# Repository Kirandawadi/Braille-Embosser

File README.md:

An autonomous device built with **AVR** and programmed in **C** that can convert any printed textbook into braille format using **Optical Character Recognition (OCR)** and custom-built hardware mechanism.

It won the 2nd runner up at **AT-HACKATHON 2018**.

**Demo Video:** [Link](https://1drv.ms/v/c/b3eb1096e4f4a3a8/Eaij9OSWEOsggLN66wAAAAABXvvN7yaE1aCTUCs381BpYw)

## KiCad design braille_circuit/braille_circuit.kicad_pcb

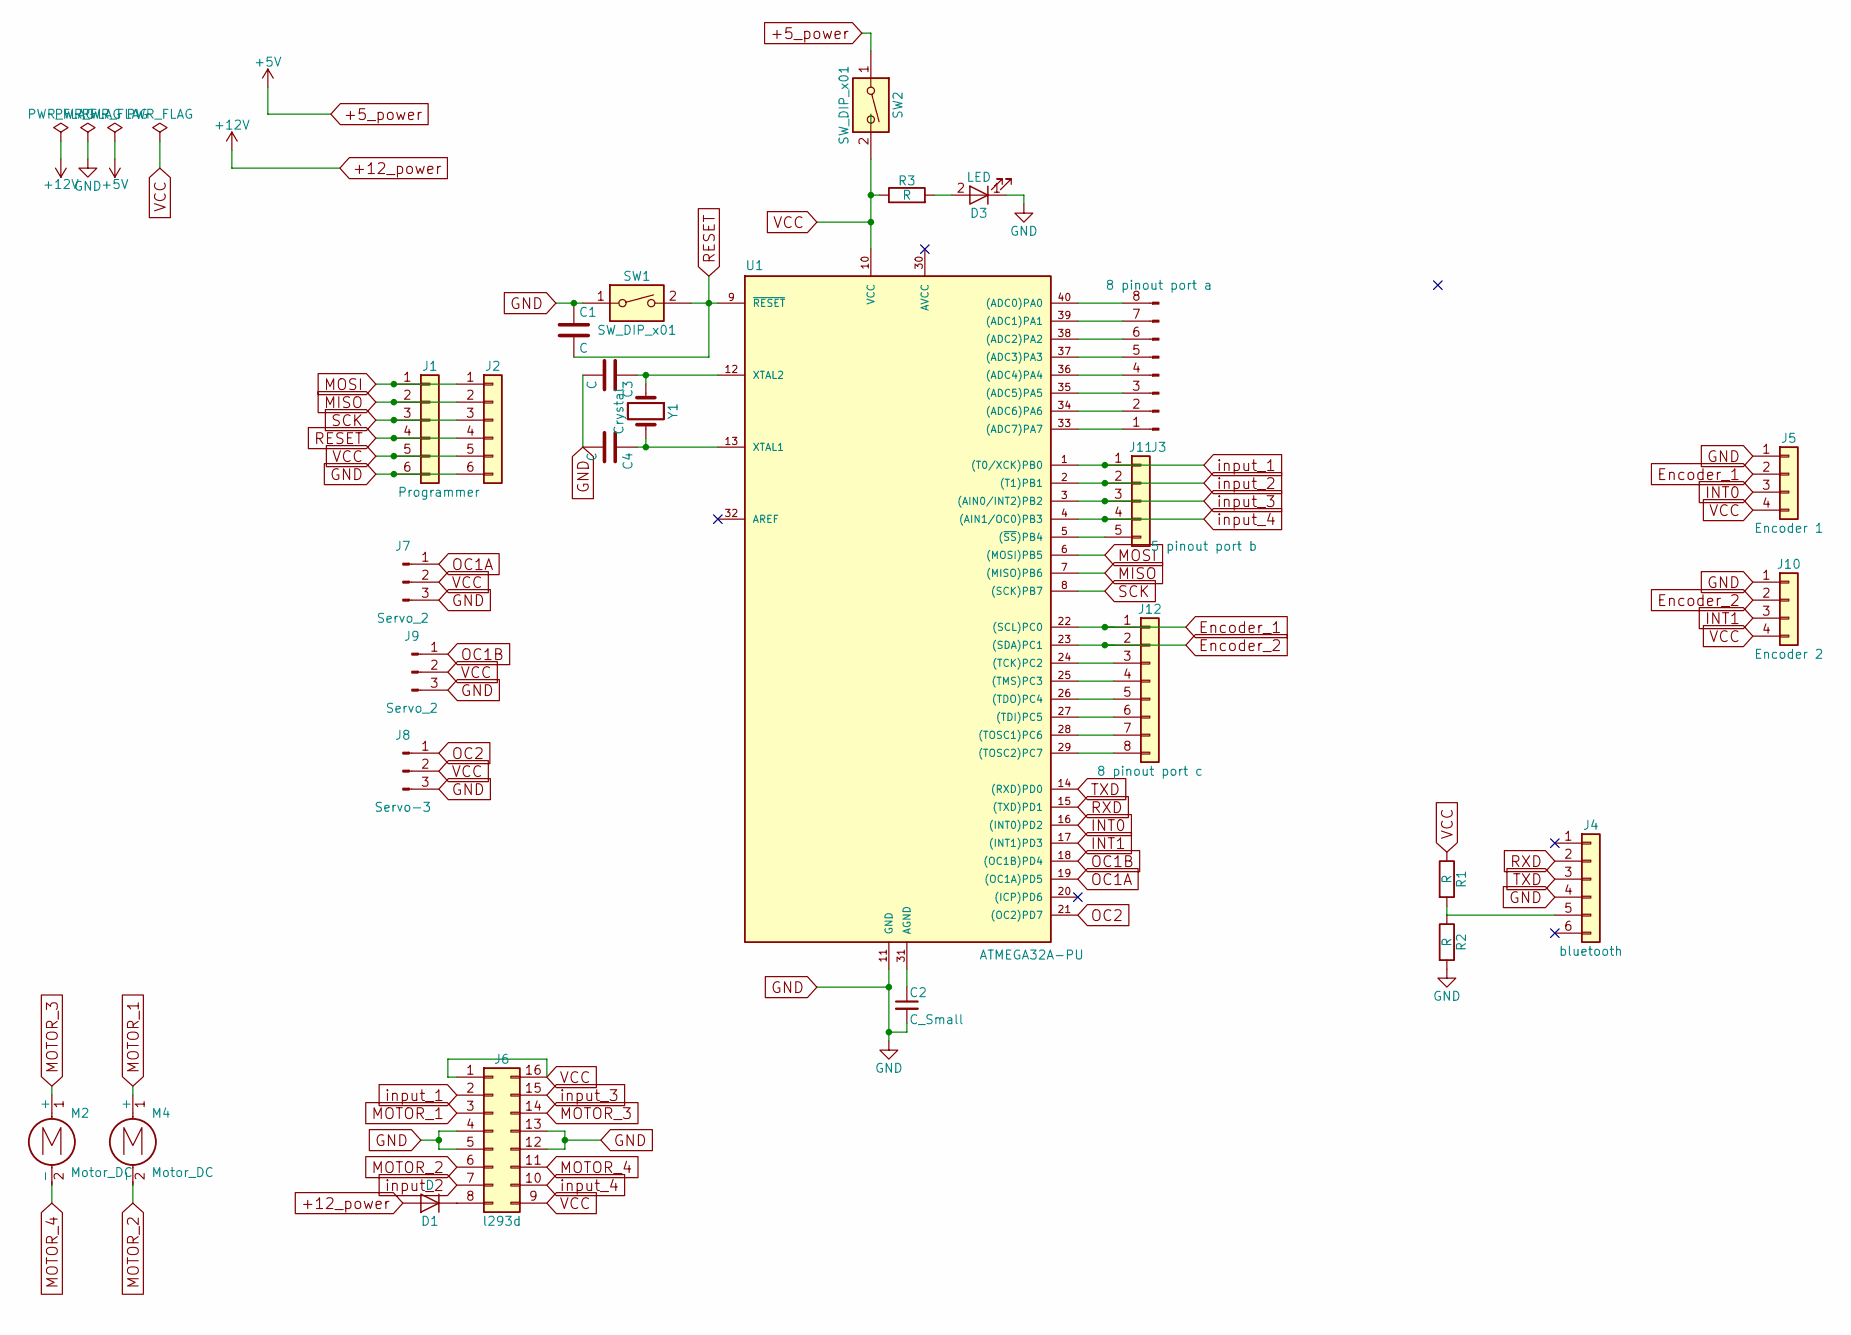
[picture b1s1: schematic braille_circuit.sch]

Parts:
C1, C3, C4: C; C_Disc_D3.0mm_W2.0mm_P2.50mm
C2: C_Small; C_Disc_D3.0mm_W2.0mm_P2.50mm
D1: D; D_5W_P10.16mm_Horizontal
D3: LED; LED_D5.0mm
J1, J2: Programmer; Pin_Header_Straight_1x06_Pitch2.54mm
J3: 8 pinout port a; Pin_Header_Straight_1x08_Pitch2.54mm
J4: bluetooth; Pin_Header_Straight_1x06_Pitch2.54mm
J5: Encoder 1; Pin_Header_Straight_1x04_Pitch2.54mm
J6: l293d; DIP-16_W7.62mm_Socket_LongPads
J7, J9: Servo_2; Pin_Header_Straight_1x03_Pitch2.54mm
J8: Servo-3; Pin_Header_Straight_1x03_Pitch2.54mm
J10: Encoder 2; Pin_Header_Straight_1x04_Pitch2.54mm
J11: 5 pinout port b; Pin_Header_Straight_1x05_Pitch2.54mm
J12: 8 pinout port c; Pin_Header_Straight_1x08_Pitch2.54mm
M2, M4: Motor_DC; TerminalBlock_Pheonix_MKDS1.5-2pol
R1, R2, R3: R; R_Axial_DIN0207_L6.3mm_D2.5mm_P10.16mm_Horizontal
SW1: SW_DIP_x01; SW_PUSH_6mm_h5mm
SW2: SW_DIP_x01; 6_pin_switch
U1: ATMEGA32A-PU; DIP-40_W15.24mm_LongPads
Y1: Crystal; Crystal_HC18-U_Vertical

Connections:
+5_power: SW2.1
+12_power: D1.2 (A)
Encoder_1: J5.2, J12.1, U1.22 ((SCL)PC0)
Encoder_2: J10.2, J12.2, U1.23 ((SDA)PC1)
GND: C1.1, C2.2, C3.2, C4.2, D3.1 (K), J1.6, J2.6, J4.4, J5.1, J6.4, J6.5, J6.12, J6.13, J7.3, J8.3, J9.3, J10.1, R2.2, SW1.1, U1.11 (GND)
INT0: J5.3, U1.16 ((INT0)PD2)
INT1: J10.3, U1.17 ((INT1)PD3)
MISO: J1.2, J2.2, U1.7 ((MISO)PB6)
MOSI: J1.1, J2.1, U1.6 ((MOSI)PB5)
MOTOR_1: J6.3, M4.1 (+)
MOTOR_2: J6.6, M4.2 (-)
MOTOR_3: J6.14, M2.1 (+)
MOTOR_4: J6.11, M2.2 (-)
unnamed: C2.1, U1.31 (AGND)
unnamed: C3.1, U1.12 (XTAL2), Y1.1
unnamed: C4.1, U1.13 (XTAL1), Y1.2
unnamed: D1.1 (K), J6.8
unnamed: D3.2 (A), R3.2
unnamed: J3.1, U1.33 ((ADC7)PA7)
unnamed: J3.2, U1.34 ((ADC6)PA6)
unnamed: J3.3, U1.35 ((ADC5)PA5)
unnamed: J3.4, U1.36 ((ADC4)PA4)
unnamed: J3.5, U1.37 ((ADC3)PA3)
unnamed: J3.6, U1.38 ((ADC2)PA2)
unnamed: J3.7, U1.39 ((ADC1)PA1)
unnamed: J3.8, U1.40 ((ADC0)PA0)
unnamed: J4.5, R1.2, R2.1
unnamed: J11.5, U1.5 ((~SS~)PB4)
unnamed: J12.3, U1.24 ((TCK)PC2)
unnamed: J12.4, U1.25 ((TMS)PC3)
unnamed: J12.5, U1.26 ((TDO)PC4)
unnamed: J12.6, U1.27 ((TDI)PC5)
unnamed: J12.7, U1.28 ((TOSC1)PC6)
unnamed: J12.8, U1.29 ((TOSC2)PC7)
OC1A: J7.1, U1.19 ((OC1A)PD5)
OC1B: J9.1, U1.18 ((OC1B)PD4)
OC2: J8.1, U1.21 ((OC2)PD7)
RESET: C1.2, J1.4, J2.4, SW1.2, U1.9 (~RESET)
RXD: J4.2, U1.15 ((TXD)PD1)
SCK: J1.3, J2.3, U1.8 ((SCK)PB7)
TXD: J4.3, U1.14 ((RXD)PD0)
VCC: J1.5, J2.5, J5.4, J6.1, J6.9, J6.16, J7.2, J8.2, J9.2, J10.4, R1.1, R3.1, SW2.2, U1.10 (VCC)
input_1: J6.2, J11.1, U1.1 ((T0/XCK)PB0)
input_2: J6.7, J11.2, U1.2 ((T1)PB1)
input_3: J6.15, J11.3, U1.3 ((AIN0/INT2)PB2)
input_4: J6.10, J11.4, U1.4 ((AIN1/OC0)PB3)

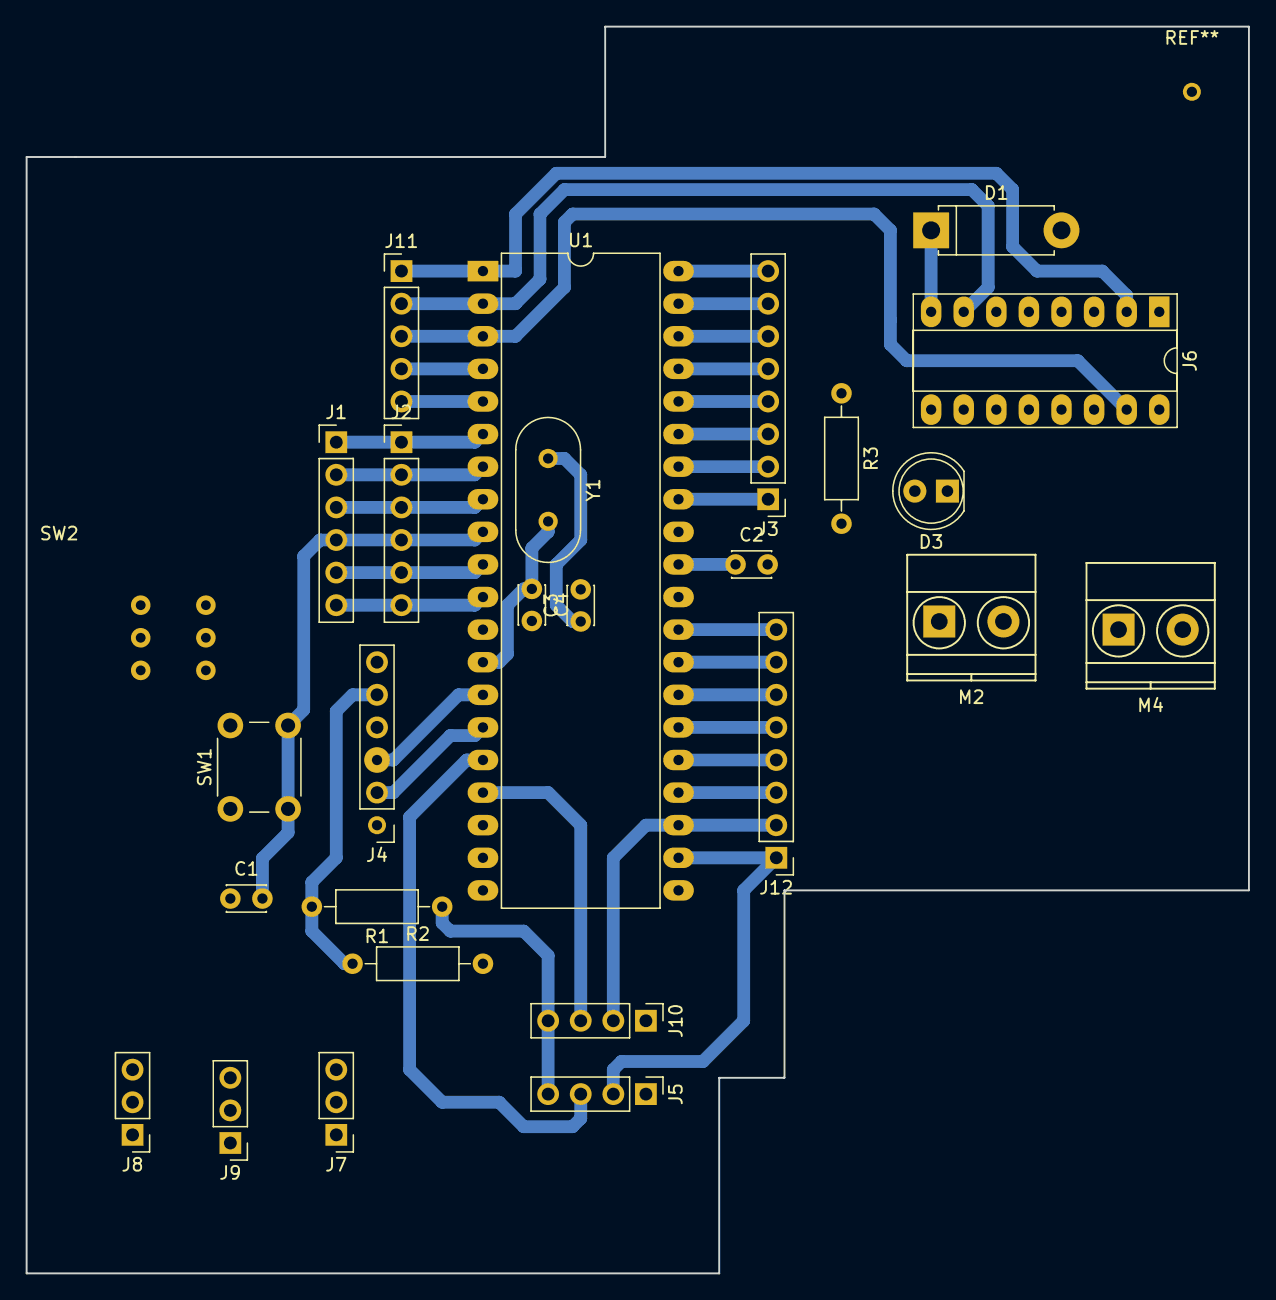
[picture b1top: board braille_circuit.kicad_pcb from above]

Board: 2 copper layers, 95.2 x 97.2 mm, 27 parts (0 on the bottom side), 44 nets.

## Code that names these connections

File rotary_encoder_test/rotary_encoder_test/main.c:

/*
 * opto_test.c
 *
 * Created: 5/13/2018 8:03:57 AM
 * Author : Acer-PC
 */ 

#define F_CPU 16000000UL
#include <avr/io.h>
#include <avr/interrupt.h>
#include <util/delay.h>
#include "USART_RS232_H_file.h"
#include "motors.h"
#include "braille_codes.h"
#include <stdio.h>
#include <stdlib.h>	
#include <ctype.h>
#include <stdlib.h>
#include <util/delay.h>
#define bit_is_set(sfr,bit) (_SFR_BYTE(sfr) & _BV(bit))
#define bit_is_clear(sfr,bit) (!(_SFR_BYTE(sfr) & _BV(bit)))

char buffer[20], float_[10];                            //used in converting number to string and then transmitting via bluetooth
char buff_[100]={0};										//used in USART
volatile double linear_counter,rotary_counter;
int test=0;
long int pulse_width=0,pre=0;
int num=0;
int rec=0,receive=0,converted;
int j=0 ;
uint8_t tem=0;
double linear_position=2;
int volatile punch_pin[6] = {0,0,0,0,0,0};

ISR(INT0_vect)				//used by linear
{
		if(((bit_is_clear(PINC,PC0))==(bit_is_clear(PIND,PD2)))||((bit_is_set(PINC,PC0))==(bit_is_set(PIND,PD2))))
		{
			--linear_counter;
			
		}
		else
		{
			++linear_counter;
		}

}

ISR(INT1_vect)			//used by rotary
{
	
	if(((bit_is_clear(PINB,PB0))==(bit_is_clear(PIND,PD3)))||((bit_is_set(PINB,PB0))==(bit_is_set(PIND,PD3))))
	{
		
		++rotary_counter;
		
	}
	else
	{
		--rotary_counter;
	}
	
}

ISR(USART_RXC_vect)
{

	/*int received = UDR;

	if(received =='a')
	{
		go_rotary_forward();
	}

	if(received == 'b')
	{
		PORTB = 0x00;
				
	}
	
		if(received =='q')
		{
			go_rotary_forward();
		}

		if(received == 'w')
		{
			go_rotary_backward();
		}
*/


}


int main(void)
{
	DDRA |= 1<<PINA1;			//Controlling relay through this pin
	PORTA |= 1<<PINA1;
	DDRC &= ~(1<<PINC0);			//making PINC0 as interrupt taker for INT0
	//DDRD &= ~(1<<PIND3);			//making INT1 as input
	DDRB = 0xFF;			//All pins are output for Motors 1 and 2
	sei();
	USART_Init(38400);
	GICR = (1<<INT0)|(1<<INT1);				//|(1<<INT2)
    MCUCR = (1<<ISC00)|(1<<ISC10);			//Both INT0 and INT1 interrupt on both edges(rising and falling)
	//MCUCSR = 1<<ISC2;						//INT2 on rising edge
	//TCCR1B |= (1<<CS12)|(1<<CS10);
	
	//double i=30;
	
	_delay_ms(2000);
 	set_position_cm(linear_position);
 	USART_SendString("Calibrating your system....\n");
	
	
	print_VISION();
	//vertical_dots();
	
	
	/*
	Braille_Print_character('a');
	//_delay_ms(2000);
	Braille_Print_character('b');
	//_delay_ms(2000);
	Braille_Print_character('c');
	//_delay_ms(2000);*/

   
		   while (1) 
		{
// 			
// 			set_position_cm(4);
// 			_delay_ms(500);
// 			set_position_cm(2);
// 			_delay_ms(500);
// 			set_position_cm(6);
// 			_delay_ms(500);
// 			set_position_cm(2);
// 			_delay_ms(500);
// 			
			
			// _delay_ms(100);
// 		
// 		go_linear_forward();
// 		_delay_ms(500);
// 		go_linear_backward();
// 		_delay_ms(500);
// 		
// 	go_rotary_forward();
// 	_delay_ms(500);
// 	rotary_halt();
// 	_delay_ms(500);
// // 			
// 		 for(int i=3;i<30;i++)
// 			 {
// 				 	set_position_cm(i);
// 					 _delay_ms(500);
// 			 }
		}


	return 0;
}




				/**********BACKUP*****************/

// go_rotary_forward();
// 
// dtostrf(i, 3, 2, float_ );
// sprintf(buffer,"Given Value= %s\t",float_);
// USART_SendString(buffer);
// 
// dtostrf(rotary_counter, 3, 2, float_ );
// sprintf(buffer,"Counter value= %s\n",float_);
// USART_SendString(buffer);
// 
// if(rotary_counter>=1086)
// {
// 	rotary_halt();
// 	break;
// }


// 
// 
// void toggle_two_time()
// {
// 	for(int i=0;i<4;i++)
// 	{
// 		PORTB^=1<<PINB0;
// 		_delay_ms(400);
// 	}
// 	
// }
// 
// void toggle_three_time()
// {
// 	for(int i=0;i<6;i++)
// 	{
// 		PORTB^=1<<PINB0;
// 		_delay_ms(400);
// 		
// 		
// 	}
// 	
// }
// 
// 
// ISR(USART_RXC_vect)
// {
// 
// 	int received = UDR;
// 	
// 	if(received =='a')
// 	{
// 		toggle_two_time();
// 	}
// 	
// 	if(received == 'b')
// 	{
// 		toggle_three_time();
// 	}
// 	
// 	
// 
// }

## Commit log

2019-02-19 Running Code
